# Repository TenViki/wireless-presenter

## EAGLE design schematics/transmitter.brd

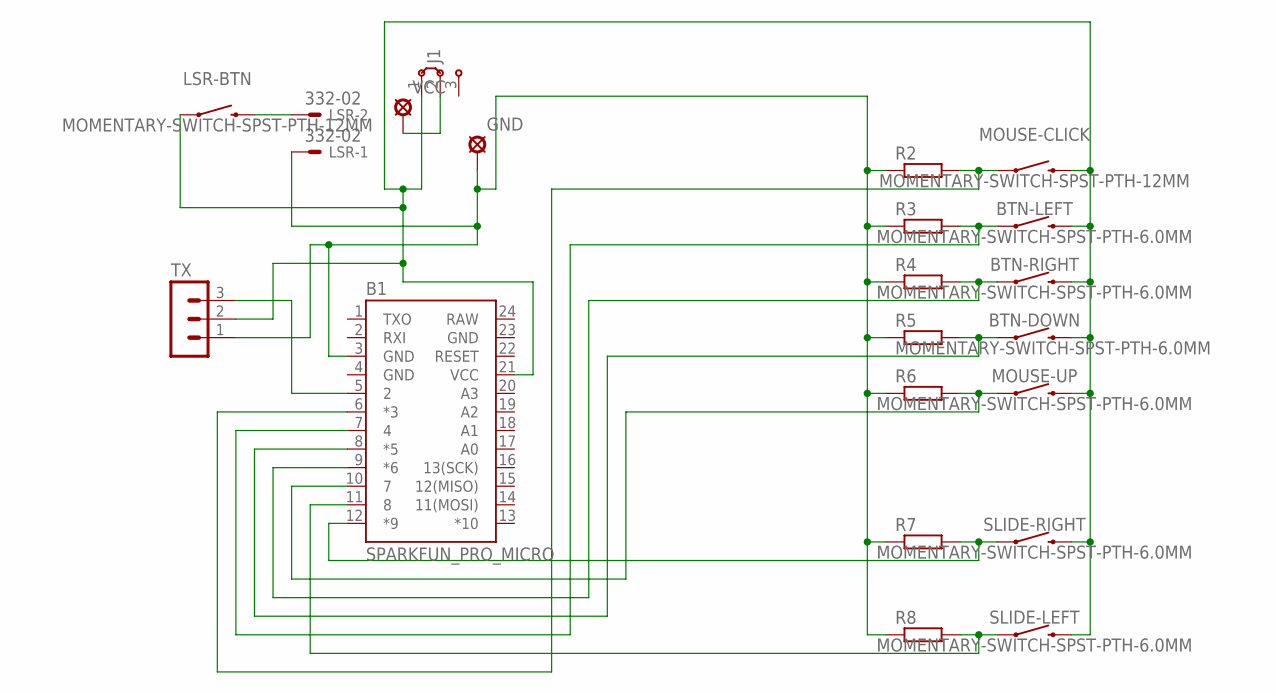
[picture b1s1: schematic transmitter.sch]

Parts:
B1: SPARKFUN_PRO_MICRO
BTN-DOWN: MOMENTARY-SWITCH-SPST-PTH-6.0MM; TACTILE_SWITCH_PTH_6.0MM
BTN-LEFT: MOMENTARY-SWITCH-SPST-PTH-6.0MM; TACTILE_SWITCH_PTH_6.0MM
BTN-RIGHT: MOMENTARY-SWITCH-SPST-PTH-6.0MM; TACTILE_SWITCH_PTH_6.0MM
GND: SE13
J1: J2X5MM; 05C
LSR: 332-02
LSR-BTN: MOMENTARY-SWITCH-SPST-PTH-12MM; TACTILE_SWITCH_PTH_12MM
MOUSE-CLICK: MOMENTARY-SWITCH-SPST-PTH-12MM; TACTILE_SWITCH_PTH_12MM
MOUSE-UP: MOMENTARY-SWITCH-SPST-PTH-6.0MM; TACTILE_SWITCH_PTH_6.0MM
R2, R3, R4, R5, R6, R7, R8: R-EU_0204/7; 0204/7
SLIDE-LEFT: MOMENTARY-SWITCH-SPST-PTH-6.0MM; TACTILE_SWITCH_PTH_6.0MM
SLIDE-RIGHT: MOMENTARY-SWITCH-SPST-PTH-6.0MM; TACTILE_SWITCH_PTH_6.0MM
TX: MA03-1
VCC: SE13

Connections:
GND: B1.4 (GND), B1.23 (GND)
unnamed: B1.9 (*6), BTN-RIGHT.1, R4.2
unnamed: B1.3 (GND), GND.MP, LSR.1, R2.1, R3.1, R4.1, R5.1, R6.1, R7.1, R8.1, TX.1
unnamed: LSR.2, LSR-BTN.3 (2)
unnamed: B1.6 (*3), MOUSE-CLICK.1, R2.2
unnamed: B1.7 (4), BTN-LEFT.1, R3.2
unnamed: J1.2, VCC.MP
unnamed: B1.8 (*5), BTN-DOWN.1, R5.2
unnamed: B1.10 (7), MOUSE-UP.1, R6.2
unnamed: B1.12 (*9), R7.2, SLIDE-RIGHT.1
unnamed: B1.11 (8), R8.2, SLIDE-LEFT.1
unnamed: B1.21 (VCC), BTN-DOWN.3 (2), BTN-LEFT.3 (2), BTN-RIGHT.3 (2), J1.1, LSR-BTN.1, MOUSE-CLICK.3 (2), MOUSE-UP.3 (2), SLIDE-LEFT.3 (2), SLIDE-RIGHT.3 (2), TX.2
unnamed: B1.5 (2), TX.3
RAW: B1.24 (RAW)

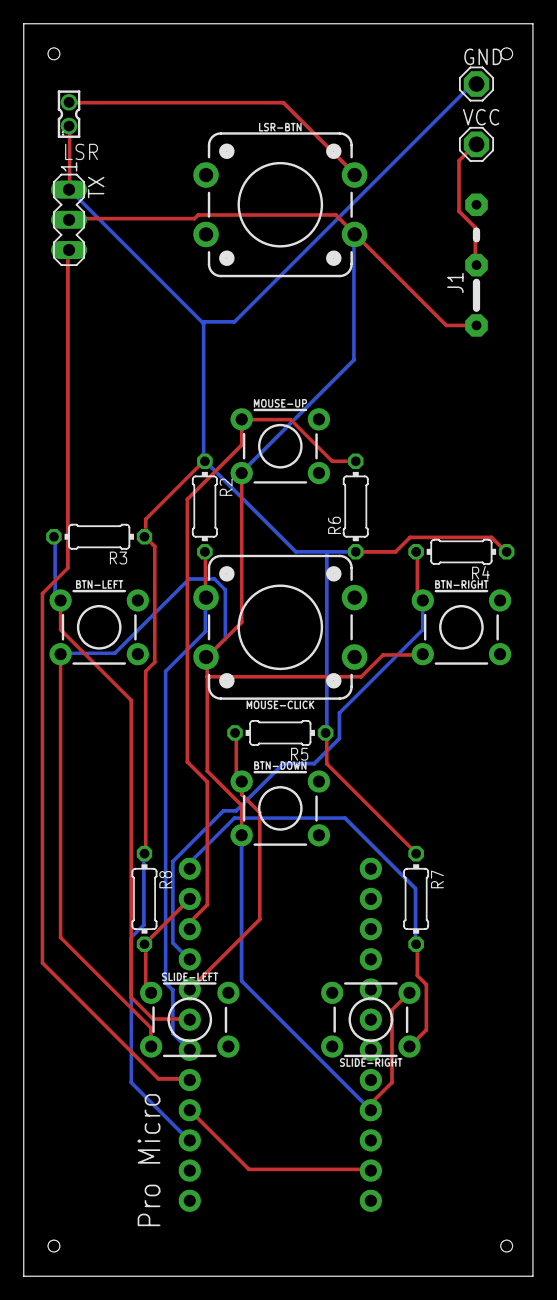
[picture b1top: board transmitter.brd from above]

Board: 2 copper layers, 42.9 x 105.4 mm, 21 parts (1 on the bottom side), 13 nets.

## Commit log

2022-05-26 :sparkles: Adds schematics
2022-06-13 :sparkles: Adds code
2022-06-13 :zap: Updates test files
2022-06-17 :zap: updates something

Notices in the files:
parts and their libraries:
SparkFun-Boards: Licensing: Creative Commons ShareAlike 4.0 International - https://creativecommons.org/licenses/by-sa/4.0
